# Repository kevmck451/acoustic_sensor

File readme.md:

# Acoustic Sensor
	- University of Memphis
	- Multiple Unmanned Ariel System Project
	- Army Research Lab

The audio recording device used in the experiment was the Sony Spresense microcontroller with custom firmware developed to enable recording across four analog channels at a 16-bit resolution and a 48 kHz sampling rate. We utilized the CMI-5247TF-K10 electret condenser microphone, recommended by Spresense documentation for its compatibility and straightforward setup with the microcontroller. This unidirectional microphone has an operational frequency range of 70 Hz to 20 kHz. Additionally, a shield circuit was designed for the microcontroller to integrate microphone inputs, potentiometers for calibrating microphone levels, an OLED display screen, and sensors for temperature, humidity, and pressure. The device’s enclosure and microphone mount were designed using CAD software and produced via 3D printing. For wind noise mitigation, the microphones were equipped with dual layers of wind protection: an initial layer consisting of thin foam covers typical for lavalier microphones, followed by wind muffs also designed for lavalier microphones. While this setup effectively reduces wind noise for winds up to 5 m/s, there remains considerable scope for enhancing physical wind noise reduction techniques.

## Read Manual.md for specific instructions on data collection

## Acoustic_Firmware
	- firmware and header files for arduino IDE upload
	- Acoustic_Firmware.ino
	- screen.h
	- temp.h

## BIN
	- this needs to be on the sony spresense formated SD card
	- includes the audio codecs used for recording
	- gain.txt file to store the default gain setting

## Docs
	- Recorder Schematic
	- Parts List
	- Recorder Versions
	- Sony Microcontroller Notes

## Enclosure
	- 3D Printer Enclosure files
	- MicModuleBoxrev3.data
	- MicModuleBoxrev3.gcode

## Shield
	- Sony Spresense Shield KiCad File
	- Mic Resisters: 2.2k Ohms
	- Capacitors: 1uF
	- Potentiometers: 500k Ohms

# Acoustic Sensor

# KiCad Model

# In Action

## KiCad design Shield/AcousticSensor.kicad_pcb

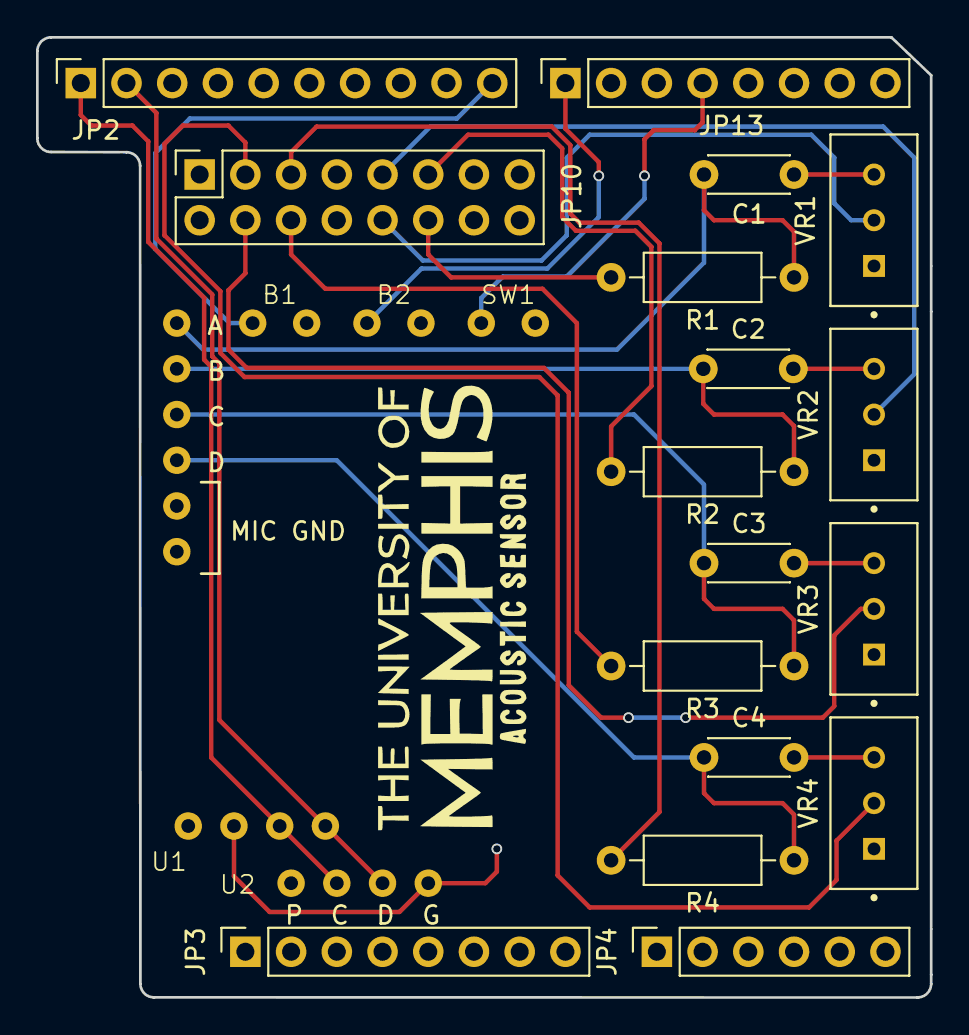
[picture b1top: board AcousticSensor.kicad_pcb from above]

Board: 4 copper layers, 49.7 x 53.3 mm, 22 parts (0 on the bottom side), 24 nets.

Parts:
B1, B2: Jumper-Cable_Button-Switch
C1, C2, C3, C4: 1u; C_Disc_D4.3mm_W1.9mm_P5.00mm
JP2: Digital/PWM; PinSocket_1x10_P2.54mm_Vertical
JP3: Power; PinSocket_1x08_P2.54mm_Vertical
JP4: Analog; PinSocket_1x06_P2.54mm_Vertical
JP10: Microphone Pins; PinSocket_2x08_P2.54mm_Vertical
JP13: Digital/PWM; PinSocket_1x08_P2.54mm_Vertical
R1, R2, R3, R4: 2.2k; R_Axial_DIN0207_L6.3mm_D2.5mm_P10.16mm_Horizontal
SW1: Jumper-Cable_Button-Switch
U1, U2: OLED_Display
VR1: MIC A; TRIM_3296W-1-103
VR2: MIC B; TRIM_3296W-1-103
VR3: MIC C; TRIM_3296W-1-103
VR4: MIC D; TRIM_3296W-1-103

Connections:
+3V3: JP3.4, U1.1 (Vin), U2.1 (Vin)
Aux: JP13.4, SW1.1
Bias A: JP10.12, R1.2
Bias B: JP10.11, R2.2
Bias C: JP10.6, R3.2
Bias D: JP10.5, R4.2
GND: B1.2, B2.2, JP2.4, JP3.6, JP3.7, JP10.1, SW1.2, U1.2 (GND), U2.4 (GND), VR1.1, VR2.1, VR3.1, VR4.1
GNDA: JP10.7, JP10.8, JP10.13, JP10.14
Gain: B2.1, JP13.1
Mic A: JP10.10, VR1.2
Mic B: JP10.9, VR2.2
Mic C: JP10.4, VR3.2
Mic D: JP10.3, VR4.2
unnamed: C1.1, VR1.3
unnamed: C2.2, VR2.3
unnamed: C3.2, VR3.3
unnamed: C4.2, VR4.3
unnamed: C1.2, R1.1
unnamed: C2.1, R2.1
unnamed: C3.1, R3.1
unnamed: C4.1, R4.1
Record: B1.1, JP2.10
SCL: JP2.1, U1.3 (SCL), U2.2 (SCL)
SDA: JP2.2, U1.4 (SDA), U2.3 (SDA)

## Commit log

2023-09-08 gain button functionality located and comments added
2023-09-08 gain text file added for default values
2023-09-08 List of versions and their functionality
2023-09-08 Adding gain adjustment functionality
2023-09-09 added all gain functionality
2023-09-09 update version 4 objectives
2023-09-10 adding operation manual
2023-09-10 deleting operation manual
2023-09-10 updated default gain screen
2023-09-11 fixed gain setting bugs
2023-09-11 adding functionality to update time during recording
2023-09-11 updated bit depth to 24
2023-09-11 added average weather data function
2023-09-11 updated version 4 features
2023-09-12 completed average weather data functionality
2023-09-12 tweaks to timer settings
2023-09-12 updated weather log settings
2023-09-12 oranizational changes
2023-09-12 recorder version syntax update
2023-09-12 add gitignore
2023-10-10 updated bit depth to 16 and gain value to screens
2023-10-27 added gain level to csv file
2024-05-27 organizational updates
